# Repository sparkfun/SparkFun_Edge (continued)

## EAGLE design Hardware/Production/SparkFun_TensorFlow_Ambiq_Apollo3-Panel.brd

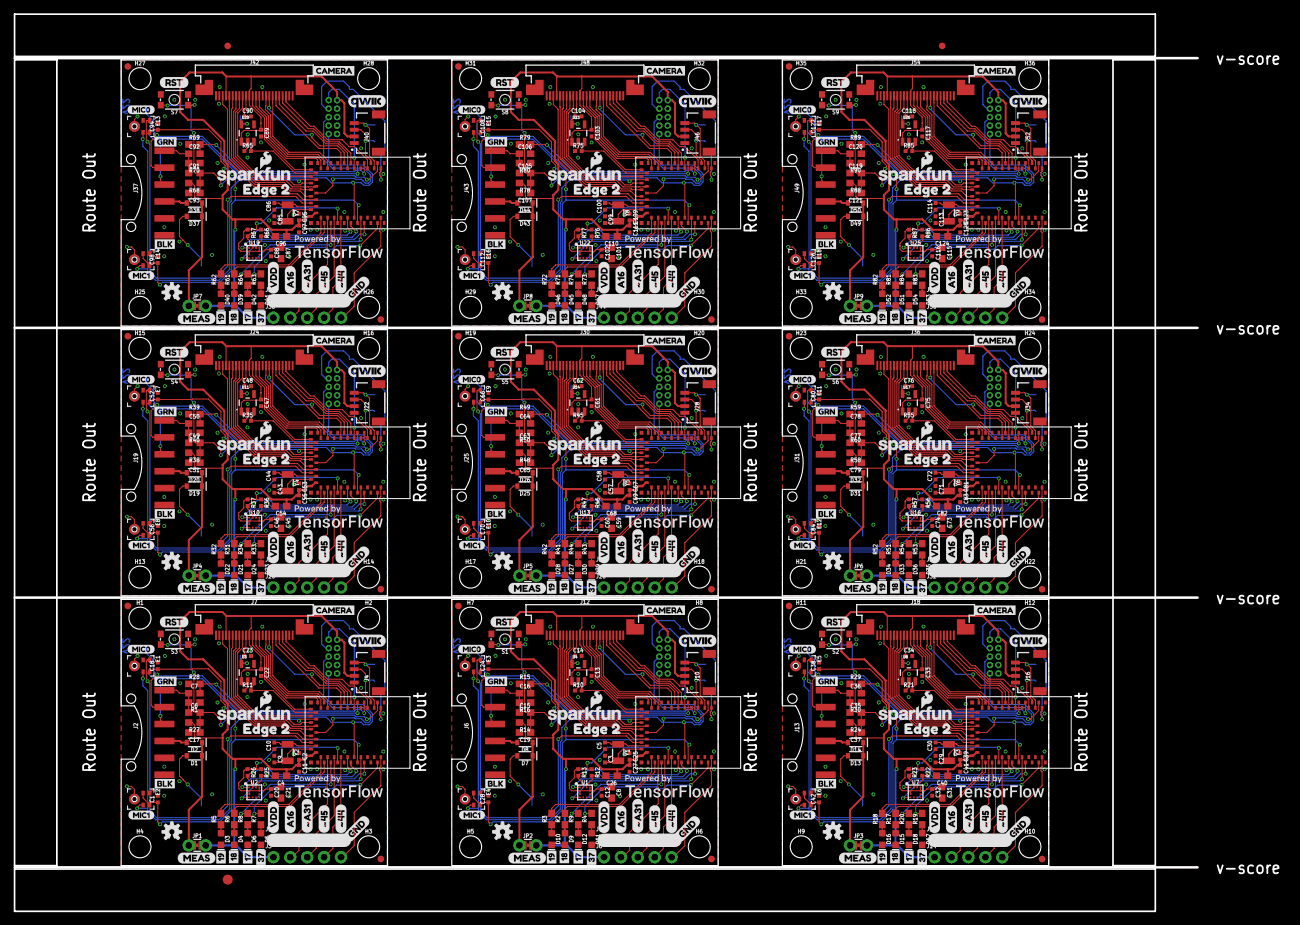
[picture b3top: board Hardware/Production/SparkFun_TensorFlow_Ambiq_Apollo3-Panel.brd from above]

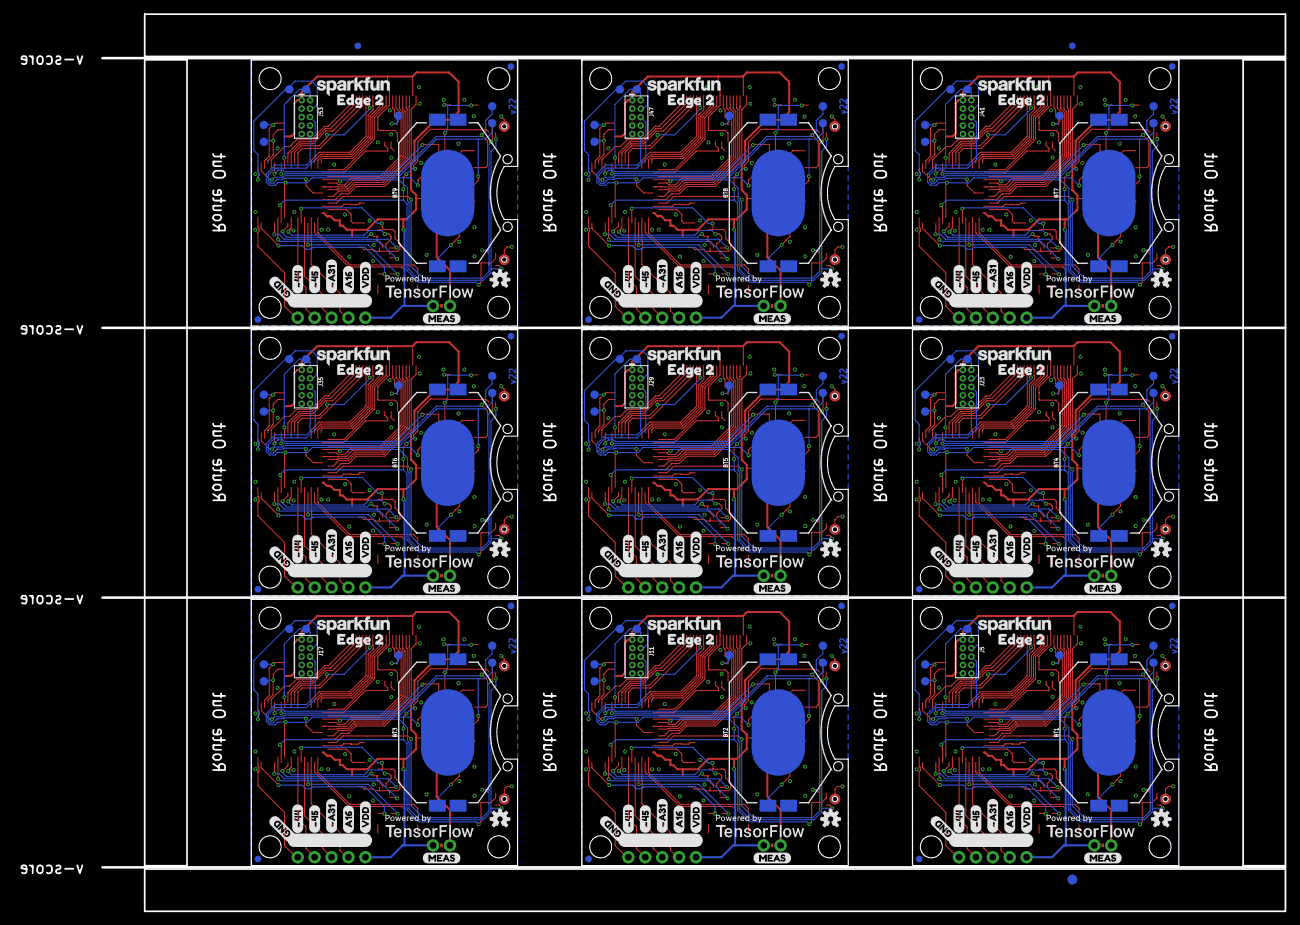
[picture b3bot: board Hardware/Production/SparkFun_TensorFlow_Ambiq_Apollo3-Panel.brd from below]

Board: 2 copper layers, 177.7 x 134.7 mm, 861 parts (201 on the bottom side), 495 nets.

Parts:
BT1, BT2, BT3, BT4, BT5, BT6, BT7, BT8, BT9: BATTCON_20MM_4LEGS_OVERPASTE_INNER
C1, C2, C12, C18, C20, C24, C25, C28, C32, C38, C39, C42, C46, C52, C53, C56, C60, C66, C67, C70, C74, C80, C81, C84, C88, C94, C95, C98, C102, C108, C109, C112, C116, C122, C123, C126: 0.1uF; 0402-TIGHT
C3, C5, C9, C10, C29, C30, C43, C44, C57, C58, C71, C72, C85, C86, C99, C100, C113, C114: 15pF; 0402-TIGHT
C4, C8, C21, C26, C31, C40, C45, C54, C59, C68, C73, C82, C87, C96, C101, C110, C115, C124: 10uF; 0603
C6, C7, C15, C16, C35, C36, C49, C50, C63, C64, C77, C78, C91, C92, C105, C106, C119, C120: 0.1uF; 0603
C11, C13, C14, C22, C23, C27, C33, C34, C41, C47, C48, C55, C61, C62, C69, C75, C76, C83, C89, C90, C97, C103, C104, C111, C117, C118, C125: 1.0uF; 0402-TIGHT
C17, C19, C37, C51, C65, C79, C93, C107, C121: 1nF; 0603
D1, D2, D7, D8, D13, D14, D19, D20, D25, D26, D31, D32, D37, D38, D43, D44, D49, D50: 1A/23V/620mV; SOD-323
D3, D10, D16, D22, D28, D34, D40, D46, D52: RED; LED-0603
D4, D9, D15, D21, D27, D33, D39, D45, D51: BLUE; LED-0603
D5, D11, D17, D23, D29, D35, D41, D47, D53: Yellow; LED-0603
D6, D12, D18, D24, D30, D36, D42, D48, D54: GREEN; LED-0603
E1, E2, E3, E4, E5, E6, E7, E8, E9, E10, E11, E12, E13, E14, E15, E16, E17, E18: SPH0641LM4H-1; SPH0641LM4H-1_MICROPHONE
E$1, E$2, E$3, E$4: FIDUCIAL-1X2
E$5, E$6: FIDUCIAL-1.5X3
FD1, FD2, FD3, FD4, FD5, FD6, FD7, FD8, FD9, FD10, FD11, FD12, FD13, FD14, FD15, FD16, FD17, FD18, FD19, FD20, FD21, FD22, FD23, FD24, FD25, FD26, FD27, FD28, FD29, FD30, FD31, FD32, FD33, FD34, FD35, FD36: FIDUCIAL1X2; FIDUCIAL-1X2
FRAME1, FRAME3, FRAME5, FRAME7, FRAME9, FRAME11, FRAME13, FRAME15, FRAME17: FRAME-LETTER; CREATIVE_COMMONS
FRAME2, FRAME4, FRAME6, FRAME8, FRAME10, FRAME12, FRAME14, FRAME16, FRAME18: FRAME-LETTERNO_PACKAGE; DUMMY
H1, H2, H3, H4, H5, H6, H7, H8, H9, H10, H11, H12, H13, H14, H15, H16, H17, H18, H19, H20, H21, H22, H23, H24, H25, H26, H27, H28, H29, H30, H31, H32, H33, H34, H35, H36: STAND-OFF
J1, J3, J8, J9, J14, J15, J20, J21, J26, J27, J32, J33, J38, J39, J44, J45, J50, J51: 1X05_NO_SILK
J2, J6, J13, J19, J25, J31, J37, J43, J49: 1X06-SMD_RA_MALE
J4, J10, J16, J22, J28, J34, J40, J46, J52: JST04_1MM_RA
J5, J11, J17, J23, J29, J35, J41, J47, J53: CORTEX_DEBUG; 2X5-PTH-1.27MM
J7, J12, J18, J24, J30, J36, J42, J48, J54: CAMERA-HIMAX; FPC-24-AMPHENOL-SFV24R-1STE1HLF
JP1, JP2, JP3, JP4, JP5, JP6, JP7, JP8, JP9: JUMPER-COMBO_2_NC_TRACE; COMBO-JUMPER_2_NC_TRACE
LOGO1, LOGO3, LOGO5, LOGO7, LOGO9, LOGO11, LOGO13, LOGO15, LOGO17: SFE_LOGO_NAME_FLAME.1_INCH; SFE_LOGO_NAME_FLAME_.1
LOGO2, LOGO4, LOGO6, LOGO8, LOGO10, LOGO12, LOGO14, LOGO16, LOGO18: OSHW-LOGOS; OSHW-LOGO-S
R1, R14, R16, R24, R27, R30, R38, R40, R48, R50, R58, R60, R68, R70, R78, R80, R88, R90: 100k; 0603
R2, R3, R4, R5, R6, R7, R8, R9, R17, R18, R19, R20, R31, R32, R33, R34, R41, R42, R43, R44, R51, R52, R53, R54, R61, R62, R63, R64, R71, R72, R73, R74, R81, R82, R83, R84: 1k; 0603
R10, R11, R12, R13, R21, R22, R23, R25, R26, R35, R36, R37, R45, R46, R47, R55, R56, R57, R65, R66, R67, R75, R76, R77, R85, R86, R87: 100k; 0402-TIGHT
R15, R28, R29, R39, R49, R59, R69, R79, R89: 220k; 0603
S1, S2, S3, S4, S5, S6, S7, S8, S9: RESET; TACTILE_SWITCH_SMD_4.6X2.8MM
TP1, TP2, TP8, TP9, TP15, TP16, TP22, TP23, TP29, TP30, TP36, TP37, TP43, TP44, TP50, TP51, TP57, TP58: PAD.03X.05
TP3, TP4, TP5, TP6, TP7, TP10, TP11, TP12, TP13, TP14, TP17, TP18, TP19, TP20, TP21, TP24, TP25, TP26, TP27, TP28, TP31, TP32, TP33, TP34, TP35, TP38, TP39, TP40, TP41, TP42, TP45, TP46, TP47, TP48, TP49, TP52, TP53, TP54, TP55, TP56, TP59, TP60, TP61, TP62, TP63: TEST-POINT3X5; PAD.03X.05
U1, U2, U7, U10, U13, U16, U19, U22, U25: LIS2DH12; LGA-12-LISDH12
U3, U4, U8, U11, U14, U17, U20, U23, U26: 1.8V; SOT23-5
U5, U6, U9, U12, U15, U18, U21, U24, U27: ARTEMIS_MODULESMD; ARTEMIS_FP
U$1, U$43, U$74, U$105, U$136, U$167, U$198, U$229, U$260: MIC00
U$2, U$37, U$68, U$99, U$130, U$161, U$192, U$223, U$254: BLK2
U$3, U$14, U$17, U$33, U$63, U$66, U$94, U$97, U$125, U$128, U$156, U$159, U$187, U$190, U$218, U$221, U$249, U$252: GND0
U$4, U$9, U$18, U$22, U$64, U$65, U$95, U$96, U$126, U$127, U$157, U$158, U$188, U$189, U$219, U$220, U$250, U$251: VDD1
U$5, U$12, U$48, U$54, U$79, U$85, U$110, U$116, U$141, U$147, U$172, U$178, U$203, U$209, U$234, U$240, U$265, U$271: #453
U$6, U$11, U$49, U$53, U$80, U$84, U$111, U$115, U$142, U$146, U$173, U$177, U$204, U$208, U$235, U$239, U$266, U$270: #A312
U$7, U$10, U$50, U$52, U$81, U$83, U$112, U$114, U$143, U$145, U$174, U$176, U$205, U$207, U$236, U$238, U$267, U$269: A161
U$8, U$51, U$82, U$113, U$144, U$175, U$206, U$237, U$268: MIC10
U$13, U$36, U$47, U$55, U$78, U$86, U$109, U$117, U$140, U$148, U$171, U$179, U$202, U$210, U$233, U$241, U$264, U$272: #444
U$15, U$32, U$56, U$60, U$87, U$91, U$118, U$122, U$149, U$153, U$180, U$184, U$211, U$215, U$242, U$246, U$273, U$277: EDGE_20
U$16, U$39, U$70, U$101, U$132, U$163, U$194, U$225, U$256: 372
U$19, U$40, U$71, U$102, U$133, U$164, U$195, U$226, U$257: QWIIC_COPYRIGHT_SMALL
U$20, U$41, U$72, U$103, U$134, U$165, U$196, U$227, U$258: CAMERA3
U$21, U$25, U$42, U$44, U$73, U$75, U$104, U$106, U$135, U$137, U$166, U$168, U$197, U$199, U$228, U$230, U$259, U$261: POWEREDBY_TF#JPG
U$23, U$57, U$88, U$119, U$150, U$181, U$212, U$243, U$274: 171
U$24, U$35, U$61, U$62, U$92, U$93, U$123, U$124, U$154, U$155, U$185, U$186, U$216, U$217, U$247, U$248, U$278, U$279: MEAS10
U$26, U$58, U$89, U$120, U$151, U$182, U$213, U$244, U$275: 182
U$27, U$34, U$67, U$98, U$129, U$160, U$191, U$222, U$253: RST15
U$28, U$38, U$69, U$100, U$131, U$162, U$193, U$224, U$255: GRN1
U$29, U$45, U$76, U$107, U$138, U$169, U$200, U$231, U$262: SFE_LOGO_NAME_.1
U$30, U$46, U$77, U$108, U$139, U$170, U$201, U$232, U$263: OSHW-LOGO-S
U$31, U$59, U$90, U$121, U$152, U$183, U$214, U$245, U$276: 193
Y1, Y2, Y3, Y4, Y5, Y6, Y7, Y8, Y9: 32.768kHz; CRYSTAL-SMD-3.2X1.5MM

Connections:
1.8V: C23.1, J7.10, TP7.P$1, U3.5
1.8V1: C14.1, J12.10, TP14.P$1, U4.5
1.8V2: C34.1, J18.10, TP21.P$1, U8.5
1.8V3: C48.1, J24.10, TP28.P$1, U11.5
1.8V4: C62.1, J30.10, TP35.P$1, U14.5
1.8V5: C76.1, J36.10, TP42.P$1, U17.5
1.8V6: C90.1, J42.10, TP49.P$1, U20.5
1.8V7: C104.1, J48.10, TP56.P$1, U23.5
1.8V8: C118.1, J54.10, TP63.P$1, U26.5
!DTR: C6.1, C7.1, J2.1, R1.2
!DTR1: C15.1, C16.1, J6.1, R16.2
!DTR2: C35.1, C36.1, J13.1, R30.2
!DTR3: C49.1, C50.1, J19.1, R40.2
!DTR4: C63.1, C64.1, J25.1, R50.2
!DTR5: C77.1, C78.1, J31.1, R60.2
!DTR6: C91.1, C92.1, J37.1, R70.2
!DTR7: C105.1, C106.1, J43.1, R80.2
!DTR8: C119.1, C120.1, J49.1, R90.2
A1: J8.2, U6.AD16
A2: J14.2, U9.AD16
A3: J20.2, U12.AD16
A4: J26.2, U15.AD16
A5: J32.2, U18.AD16
A6: J38.2, U21.AD16
A7: J44.2, U24.AD16
A8: J50.2, U27.AD16
A16: J3.2, U5.AD16
ACCEL_I2C_SCL: U2.1, U5.~D42
ACCEL_I2C_SCL1: U1.1, U6.~D42
ACCEL_I2C_SCL2: U7.1, U9.~D42
ACCEL_I2C_SCL3: U10.1, U12.~D42
ACCEL_I2C_SCL4: U13.1, U15.~D42
ACCEL_I2C_SCL5: U16.1, U18.~D42
ACCEL_I2C_SCL6: U19.1, U21.~D42
ACCEL_I2C_SCL7: U22.1, U24.~D42
ACCEL_I2C_SCL8: U25.1, U27.~D42
ACCEL_I2C_SDA: U2.4, U5.~D43
ACCEL_I2C_SDA1: U1.4, U6.~D43
ACCEL_I2C_SDA2: U7.4, U9.~D43
ACCEL_I2C_SDA3: U10.4, U12.~D43
ACCEL_I2C_SDA4: U13.4, U15.~D43
ACCEL_I2C_SDA5: U16.4, U18.~D43
ACCEL_I2C_SDA6: U19.4, U21.~D43
ACCEL_I2C_SDA7: U22.4, U24.~D43
ACCEL_I2C_SDA8: U25.4, U27.~D43
ACCEL_INT1: R26.2, U2.12, U5.D2
ACCEL_INT2: R25.2, U2.11, U5.D1
ACCEL_INT3: R13.2, U1.12, U6.D2
ACCEL_INT4: R12.2, U1.11, U6.D1
ACCEL_INT5: R23.2, U7.12, U9.D2
ACCEL_INT6: R22.2, U7.11, U9.D1
ACCEL_INT7: R37.2, U10.12, U12.D2
ACCEL_INT8: R36.2, U10.11, U12.D1
ACCEL_INT9: R47.2, U13.12, U15.D2
ACCEL_INT10: R46.2, U13.11, U15.D1
ACCEL_INT11: R57.2, U16.12, U18.D2
ACCEL_INT12: R56.2, U16.11, U18.D1
ACCEL_INT13: R67.2, U19.12, U21.D2
ACCEL_INT14: R66.2, U19.11, U21.D1
ACCEL_INT15: R77.2, U22.12, U24.D2
ACCEL_INT16: R76.2, U22.11, U24.D1
ACCEL_INT17: R87.2, U25.12, U27.D2
ACCEL_INT18: R86.2, U25.11, U27.D1
AMBIQ_!RST: C6.2, C17.1, J5.10, R27.1, S3.3, S3.4, U5.~RST
AMBIQ_!RST1: C15.2, C19.1, J11.10, R14.1, S1.3, S1.4, U6.~RST
AMBIQ_!RST2: C35.2, C37.1, J17.10, R24.1, S2.3, S2.4, U9.~RST
AMBIQ_!RST3: C49.2, C51.1, J23.10, R38.1, S4.3, S4.4, U12.~RST
AMBIQ_!RST4: C63.2, C65.1, J29.10, R48.1, S5.3, S5.4, U15.~RST
AMBIQ_!RST5: C77.2, C79.1, J35.10, R58.1, S6.3, S6.4, U18.~RST
AMBIQ_!RST6: C91.2, C93.1, J41.10, R68.1, S7.3, S7.4, U21.~RST
AMBIQ_!RST7: C105.2, C107.1, J47.10, R78.1, S8.3, S8.4, U24.~RST
AMBIQ_!RST8: C119.2, C121.1, J53.10, R88.1, S9.3, S9.4, U27.~RST
BOOT: C7.2, R28.2, U5.BOOT
BOOT1: C16.2, R15.2, U6.BOOT
BOOT2: C36.2, R29.2, U9.BOOT
BOOT3: C50.2, R39.2, U12.BOOT
BOOT4: C64.2, R49.2, U15.BOOT
BOOT5: C78.2, R59.2, U18.BOOT
BOOT6: C92.2, R69.2, U21.BOOT
BOOT7: C106.2, R79.2, U24.BOOT
BOOT8: C120.2, R89.2, U27.BOOT
CAMERA_D0: J7.14, U5.D14
CAMERA_D1: J7.3, U5.~AD11
CAMERA_D2: J7.9, U5.~D25
CAMERA_D3: J7.5, U5.AD34
CAMERA_D4: J7.12, U5.~D6
CAMERA_D5: J7.20, U5.~D5
CAMERA_D6: J7.19, U5.~AD35
CAMERA_D7: J7.13, U5.~D28
CAMERA_D8: J12.5, U6.AD34
CAMERA_D9: J12.3, U6.~AD11
CAMERA_D10: J12.9, U6.~D25
CAMERA_D11: J12.12, U6.~D6
CAMERA_D12: J12.14, U6.D14
CAMERA_D13: J12.13, U6.~D28
CAMERA_D14: J12.19, U6.~AD35
CAMERA_D15: J12.20, U6.~D5
CAMERA_D16: J18.5, U9.AD34
CAMERA_D17: J18.3, U9.~AD11
CAMERA_D18: J18.9, U9.~D25
CAMERA_D19: J18.12, U9.~D6
CAMERA_D20: J18.14, U9.D14
CAMERA_D21: J18.13, U9.~D28
CAMERA_D22: J18.19, U9.~AD35
CAMERA_D23: J18.20, U9.~D5
CAMERA_D24: J24.5, U12.AD34
CAMERA_D25: J24.3, U12.~AD11
CAMERA_D26: J24.9, U12.~D25
CAMERA_D27: J24.12, U12.~D6
CAMERA_D28: J24.14, U12.D14
CAMERA_D29: J24.13, U12.~D28
CAMERA_D30: J24.19, U12.~AD35
CAMERA_D31: J24.20, U12.~D5
CAMERA_D32: J30.5, U15.AD34
CAMERA_D33: J30.3, U15.~AD11
CAMERA_D34: J30.9, U15.~D25
CAMERA_D35: J30.12, U15.~D6
CAMERA_D36: J30.14, U15.D14
CAMERA_D37: J30.13, U15.~D28
CAMERA_D38: J30.19, U15.~AD35
CAMERA_D39: J30.20, U15.~D5
CAMERA_D40: J36.5, U18.AD34
CAMERA_D41: J36.3, U18.~AD11
CAMERA_D42: J36.9, U18.~D25
CAMERA_D43: J36.12, U18.~D6
CAMERA_D44: J36.14, U18.D14
CAMERA_D45: J36.13, U18.~D28
CAMERA_D46: J36.19, U18.~AD35
CAMERA_D47: J36.20, U18.~D5
CAMERA_D48: J42.5, U21.AD34
CAMERA_D49: J42.3, U21.~AD11
CAMERA_D50: J42.9, U21.~D25
CAMERA_D51: J42.12, U21.~D6
CAMERA_D52: J42.14, U21.D14
CAMERA_D53: J42.13, U21.~D28
CAMERA_D54: J42.19, U21.~AD35
CAMERA_D55: J42.20, U21.~D5
CAMERA_D56: J48.5, U24.AD34
CAMERA_D57: J48.3, U24.~AD11
CAMERA_D58: J48.9, U24.~D25
CAMERA_D59: J48.12, U24.~D6
CAMERA_D60: J48.14, U24.D14
CAMERA_D61: J48.13, U24.~D28
CAMERA_D62: J48.19, U24.~AD35
CAMERA_D63: J48.20, U24.~D5
CAMERA_D64: J54.5, U27.AD34
CAMERA_D65: J54.3, U27.~AD11
CAMERA_D66: J54.9, U27.~D25
CAMERA_D67: J54.12, U27.~D6
CAMERA_D68: J54.14, U27.D14
CAMERA_D69: J54.13, U27.~D28
CAMERA_D70: J54.19, U27.~AD35
CAMERA_D71: J54.20, U27.~D5
CAMERA_DVDD_EN: R11.2, U3.3, U5.~AD32
CAMERA_DVDD_EN1: R10.2, U4.3, U6.~AD32
CAMERA_DVDD_EN2: R21.2, U8.3, U9.~AD32
CAMERA_DVDD_EN3: R35.2, U11.3, U12.~AD32
CAMERA_DVDD_EN4: R45.2, U14.3, U15.~AD32
CAMERA_DVDD_EN5: R55.2, U17.3, U18.~AD32
CAMERA_DVDD_EN6: R65.2, U20.3, U21.~AD32
CAMERA_DVDD_EN7: R75.2, U23.3, U24.~AD32
CAMERA_DVDD_EN8: R85.2, U26.3, U27.~AD32
CAMERA_HSYNC: J7.16, U5.~D27
CAMERA_HSYNC1: J12.16, U6.~D27
CAMERA_HSYNC2: J18.16, U9.~D27
CAMERA_HSYNC3: J24.16, U12.~D27
CAMERA_HSYNC4: J30.16, U15.~D27
CAMERA_HSYNC5: J36.16, U18.~D27
CAMERA_HSYNC6: J42.16, U21.~D27
CAMERA_HSYNC7: J48.16, U24.~D27
CAMERA_HSYNC8: J54.16, U27.~D27
CAMERA_I2C_SCL: J7.21, U5.D8
CAMERA_I2C_SCL1: J12.21, U6.D8
CAMERA_I2C_SCL2: J18.21, U9.D8
CAMERA_I2C_SCL3: J24.21, U12.D8
CAMERA_I2C_SCL4: J30.21, U15.D8
CAMERA_I2C_SCL5: J36.21, U18.D8
CAMERA_I2C_SCL6: J42.21, U21.D8
CAMERA_I2C_SCL7: J48.21, U24.D8
CAMERA_I2C_SCL8: J54.21, U27.D8
CAMERA_I2C_SDA: J7.22, U5.D9
CAMERA_I2C_SDA1: J12.22, U6.D9
CAMERA_I2C_SDA2: J18.22, U9.D9
CAMERA_I2C_SDA3: J24.22, U12.D9
CAMERA_I2C_SDA4: J30.22, U15.D9
CAMERA_I2C_SDA5: J36.22, U18.D9
CAMERA_I2C_SDA6: J42.22, U21.D9
CAMERA_I2C_SDA7: J48.22, U24.D9
CAMERA_I2C_SDA8: J54.22, U27.D9
CAMERA_INT: J7.18, U5.~D23
CAMERA_INT1: J12.18, U6.~D23
CAMERA_INT2: J18.18, U9.~D23
CAMERA_INT3: J24.18, U12.~D23
CAMERA_INT4: J30.18, U15.~D23
CAMERA_INT5: J36.18, U18.~D23
CAMERA_INT6: J42.18, U21.~D23
CAMERA_INT7: J48.18, U24.~D23
CAMERA_INT8: J54.18, U27.~D23
CAMERA_MCLK: J7.8, U5.~D26
CAMERA_MCLK1: J12.8, U6.~D26
CAMERA_MCLK2: J18.8, U9.~D26
CAMERA_MCLK3: J24.8, U12.~D26
CAMERA_MCLK4: J30.8, U15.~D26
CAMERA_MCLK5: J36.8, U18.~D26
CAMERA_MCLK6: J42.8, U21.~D26
CAMERA_MCLK7: J48.8, U24.~D26
CAMERA_MCLK8: J54.8, U27.~D26
CAMERA_PCLK: J7.17, U5.D7
CAMERA_PCLK1: J12.17, U6.D7
CAMERA_PCLK2: J18.17, U9.D7
CAMERA_PCLK3: J24.17, U12.D7
CAMERA_PCLK4: J30.17, U15.D7
CAMERA_PCLK5: J36.17, U18.D7
CAMERA_PCLK6: J42.17, U21.D7
CAMERA_PCLK7: J48.17, U24.D7
CAMERA_PCLK8: J54.17, U27.D7
CAMERA_TRIG: J7.7, U5.~AD13
CAMERA_TRIG1: J12.7, U6.~AD13
CAMERA_TRIG2: J18.7, U9.~AD13
CAMERA_TRIG3: J24.7, U12.~AD13
CAMERA_TRIG4: J30.7, U15.~AD13
CAMERA_TRIG5: J36.7, U18.~AD13
CAMERA_TRIG6: J42.7, U21.~AD13
CAMERA_TRIG7: J48.7, U24.~AD13
CAMERA_TRIG8: J54.7, U27.~AD13
CAMERA_VSYNC: J7.6, U5.D15
CAMERA_VSYNC1: J12.6, U6.D15
CAMERA_VSYNC2: J18.6, U9.D15
CAMERA_VSYNC3: J24.6, U12.D15
CAMERA_VSYNC4: J30.6, U15.D15
CAMERA_VSYNC5: J36.6, U18.D15
CAMERA_VSYNC6: J42.6, U21.D15
CAMERA_VSYNC7: J48.6, U24.D15
CAMERA_VSYNC8: J54.6, U27.D15
FTDI_VCC: D2.A, J2.4
FTDI_VCC1: D8.A, J6.4
FTDI_VCC2: D14.A, J13.4
FTDI_VCC3: D20.A, J19.4
FTDI_VCC4: D26.A, J25.4
FTDI_VCC5: D32.A, J31.4
FTDI_VCC6: D38.A, J37.4
FTDI_VCC7: D44.A, J43.4
FTDI_VCC8: D50.A, J49.4
GND: BT1.2, C1.2, C2.1, C4.2, C9.1, C10.1, C11.2, C17.2, C18.2, C20.2, C21.2, C22.2, C23.2, D3.C, D4.C, D5.C, D6.C, E1.2, E1.3, E1.6, E1.7, E1.8, E2.3, E2.6, E2.7, E2.8, J1.1, J1.2, J1.3, J1.4, J1.5, J2.6, J4.1, J5.3, J5.5, J5.9, J7.2, J7.15, R1.1, R11.1, R28.1, S3.1, S3.2, U2.5, U2.6, U2.7, U2.8, U3.2, U5.GND@1, U5.GND@22, U5.GND@38, U5.GND@39, U5.GND@47, U5.GND@59
GND1: BT2.2, C3.1, C5.1, C8.2, C12.2, C13.2, C14.2, C19.2, C24.2, C25.1, C26.2, C27.2, C28.2, D9.C, D10.C, D11.C, D12.C, E3.2, E3.3, E3.6, E3.7, E3.8, E4.3, E4.6, E4.7, E4.8, J6.6, J9.1, J9.2, J9.3, J9.4, J9.5, J10.1, J11.3, J11.5, J11.9, J12.2, J12.15, R10.1, R15.1, R16.1, S1.1, S1.2, U1.5, U1.6, U1.7, U1.8, U4.2, U6.GND@1, U6.GND@22, U6.GND@38, U6.GND@39, U6.GND@47, U6.GND@59
GND2: BT3.2, C29.1, C30.1, C31.2, C32.2, C33.2, C34.2, C37.2, C38.2, C39.1, C40.2, C41.2, C42.2, D15.C, D16.C, D17.C, D18.C, E5.2, E5.3, E5.6, E5.7, E5.8, E6.3, E6.6, E6.7, E6.8, J13.6, J15.1, J15.2, J15.3, J15.4, J15.5, J16.1, J17.3, J17.5, J17.9, J18.2, J18.15, R21.1, R29.1, R30.1, S2.1, S2.2, U7.5, U7.6, U7.7, U7.8, U8.2, U9.GND@1, U9.GND@22, U9.GND@38, U9.GND@39, U9.GND@47, U9.GND@59
GND3: BT4.2, C43.1, C44.1, C45.2, C46.2, C47.2, C48.2, C51.2, C52.2, C53.1, C54.2, C55.2, C56.2, D21.C, D22.C, D23.C, D24.C, E7.2, E7.3, E7.6, E7.7, E7.8, E8.3, E8.6, E8.7, E8.8, J19.6, J21.1, J21.2, J21.3, J21.4, J21.5, J22.1, J23.3, J23.5, J23.9, J24.2, J24.15, R35.1, R39.1, R40.1, S4.1, S4.2, U10.5, U10.6, U10.7, U10.8, U11.2, U12.GND@1, U12.GND@22, U12.GND@38, U12.GND@39, U12.GND@47, U12.GND@59
GND4: BT5.2, C57.1, C58.1, C59.2, C60.2, C61.2, C62.2, C65.2, C66.2, C67.1, C68.2, C69.2, C70.2, D27.C, D28.C, D29.C, D30.C, E9.2, E9.3, E9.6, E9.7, E9.8, E10.3, E10.6, E10.7, E10.8, J25.6, J27.1, J27.2, J27.3, J27.4, J27.5, J28.1, J29.3, J29.5, J29.9, J30.2, J30.15, R45.1, R49.1, R50.1, S5.1, S5.2, U13.5, U13.6, U13.7, U13.8, U14.2, U15.GND@1, U15.GND@22, U15.GND@38, U15.GND@39, U15.GND@47, U15.GND@59
GND5: BT6.2, C71.1, C72.1, C73.2, C74.2, C75.2, C76.2, C79.2, C80.2, C81.1, C82.2, C83.2, C84.2, D33.C, D34.C, D35.C, D36.C, E11.2, E11.3, E11.6, E11.7, E11.8, E12.3, E12.6, E12.7, E12.8, J31.6, J33.1, J33.2, J33.3, J33.4, J33.5, J34.1, J35.3, J35.5, J35.9, J36.2, J36.15, R55.1, R59.1, R60.1, S6.1, S6.2, U16.5, U16.6, U16.7, U16.8, U17.2, U18.GND@1, U18.GND@22, U18.GND@38, U18.GND@39, U18.GND@47, U18.GND@59
GND6: BT7.2, C85.1, C86.1, C87.2, C88.2, C89.2, C90.2, C93.2, C94.2, C95.1, C96.2, C97.2, C98.2, D39.C, D40.C, D41.C, D42.C, E13.2, E13.3, E13.6, E13.7, E13.8, E14.3, E14.6, E14.7, E14.8, J37.6, J39.1, J39.2, J39.3, J39.4, J39.5, J40.1, J41.3, J41.5, J41.9, J42.2, J42.15, R65.1, R69.1, R70.1, S7.1, S7.2, U19.5, U19.6, U19.7, U19.8, U20.2, U21.GND@1, U21.GND@22, U21.GND@38, U21.GND@39, U21.GND@47, U21.GND@59
GND7: BT8.2, C99.1, C100.1, C101.2, C102.2, C103.2, C104.2, C107.2, C108.2, C109.1, C110.2, C111.2, C112.2, D45.C, D46.C, D47.C, D48.C, E15.2, E15.3, E15.6, E15.7, E15.8, E16.3, E16.6, E16.7, E16.8, J43.6, J45.1, J45.2, J45.3, J45.4, J45.5, J46.1, J47.3, J47.5, J47.9, J48.2, J48.15, R75.1, R79.1, R80.1, S8.1, S8.2, U22.5, U22.6, U22.7, U22.8, U23.2, U24.GND@1, U24.GND@22, U24.GND@38, U24.GND@39, U24.GND@47, U24.GND@59
GND8: BT9.2, C113.1, C114.1, C115.2, C116.2, C117.2, C118.2, C121.2, C122.2, C123.1, C124.2, C125.2, C126.2, D51.C, D52.C, D53.C, D54.C, E17.2, E17.3, E17.6, E17.7, E17.8, E18.3, E18.6, E18.7, E18.8, J49.6, J51.1, J51.2, J51.3, J51.4, J51.5, J52.1, J53.3, J53.5, J53.9, J54.2, J54.15, R85.1, R89.1, R90.1, S9.1, S9.2, U25.5, U25.6, U25.7, U25.8, U26.2, U27.GND@1, U27.GND@22, U27.GND@38, U27.GND@39, U27.GND@47, U27.GND@59
LED_BLUE: R6.2, U5.~D18
LED_BLUE1: R2.2, U6.~D18
LED_BLUE2: R17.2, U9.~D18
LED_BLUE3: R31.2, U12.~D18
LED_BLUE4: R41.2, U15.~D18
LED_BLUE5: R51.2, U18.~D18
LED_BLUE6: R61.2, U21.~D18
LED_BLUE7: R71.2, U24.~D18
LED_BLUE8: R81.2, U27.~D18
LED_GREEN: R8.2, U5.D17
LED_GREEN1: R9.2, U6.D17
LED_GREEN2: R20.2, U9.D17
LED_GREEN3: R34.2, U12.D17
LED_GREEN4: R44.2, U15.D17
LED_GREEN5: R54.2, U18.D17
LED_GREEN6: R64.2, U21.D17
LED_GREEN7: R74.2, U24.D17
LED_GREEN8: R84.2, U27.D17
LED_RED: R5.2, U5.~D19
LED_RED1: R3.2, U6.~D19
LED_RED2: R18.2, U9.~D19
LED_RED3: R32.2, U12.~D19
LED_RED4: R42.2, U15.~D19
LED_RED5: R52.2, U18.~D19
LED_RED6: R62.2, U21.~D19
LED_RED7: R72.2, U24.~D19
LED_RED8: R82.2, U27.~D19
LED_YELLOW: R7.2, U5.~D37
LED_YELLOW1: R4.2, U6.~D37
LED_YELLOW2: R19.2, U9.~D37
LED_YELLOW3: R33.2, U12.~D37
LED_YELLOW4: R43.2, U15.~D37
LED_YELLOW5: R53.2, U18.~D37
LED_YELLOW6: R63.2, U21.~D37
LED_YELLOW7: R73.2, U24.~D37
LED_YELLOW8: R83.2, U27.~D37
MIC_CLK: E1.4, E2.4, U5.~AD12
MIC_CLK1: E3.4, E4.4, U6.~AD12
MIC_CLK2: E5.4, E6.4, U9.~AD12
MIC_CLK3: E7.4, E8.4, U12.~AD12
MIC_CLK4: E9.4, E10.4, U15.~AD12
MIC_CLK5: E11.4, E12.4, U18.~AD12
MIC_CLK6: E13.4, E14.4, U21.~AD12
MIC_CLK7: E15.4, E16.4, U24.~AD12
MIC_CLK8: E17.4, E18.4, U27.~AD12
MIC_DATA: E1.1, E2.1, U5.~AD29
MIC_DATA1: E3.1, E4.1, U6.~AD29
MIC_DATA2: E5.1, E6.1, U9.~AD29
MIC_DATA3: E7.1, E8.1, U12.~AD29
MIC_DATA4: E9.1, E10.1, U15.~AD29
MIC_DATA5: E11.1, E12.1, U18.~AD29
MIC_DATA6: E13.1, E14.1, U21.~AD29
MIC_DATA7: E15.1, E16.1, U24.~AD29
MIC_DATA8: E17.1, E18.1, U27.~AD29
unnamed: D9.A, R2.1
unnamed: C9.2, U5.XI, Y2.P$2
unnamed: D10.A, R3.1
unnamed: D11.A, R4.1
unnamed: D4.A, R6.1
unnamed: D3.A, R5.1
unnamed: D5.A, R7.1
unnamed: D6.A, R8.1
unnamed: D12.A, R9.1
unnamed: C3.2, U6.XI, Y1.P$2
unnamed: D15.A, R17.1
unnamed: D16.A, R18.1
unnamed: D17.A, R19.1
unnamed: D18.A, R20.1
unnamed: C29.2, U9.XI, Y3.P$2
unnamed: D21.A, R31.1
unnamed: D22.A, R32.1
unnamed: D23.A, R33.1
unnamed: D24.A, R34.1
unnamed: C43.2, U12.XI, Y4.P$2
unnamed: D27.A, R41.1
unnamed: D28.A, R42.1
unnamed: D29.A, R43.1
unnamed: D30.A, R44.1
unnamed: C57.2, U15.XI, Y5.P$2
unnamed: D33.A, R51.1
unnamed: D34.A, R52.1
unnamed: D35.A, R53.1
unnamed: D36.A, R54.1
unnamed: C71.2, U18.XI, Y6.P$2
unnamed: D39.A, R61.1
unnamed: D40.A, R62.1
unnamed: D41.A, R63.1
unnamed: D42.A, R64.1
unnamed: C85.2, U21.XI, Y7.P$2
unnamed: D45.A, R71.1
unnamed: D46.A, R72.1
unnamed: D47.A, R73.1
unnamed: D48.A, R74.1
unnamed: C99.2, U24.XI, Y8.P$2
unnamed: D51.A, R81.1
unnamed: D52.A, R82.1
unnamed: D53.A, R83.1
unnamed: D54.A, R84.1
unnamed: C113.2, U27.XI, Y9.P$2
QWIIC_SCL: J4.4, TP3.P$1, U5.~D39
QWIIC_SCL1: J10.4, TP10.P$1, U6.~D39
QWIIC_SCL2: J16.4, TP17.P$1, U9.~D39
QWIIC_SCL3: J22.4, TP24.P$1, U12.~D39
QWIIC_SCL4: J28.4, TP31.P$1, U15.~D39
QWIIC_SCL5: J34.4, TP38.P$1, U18.~D39
QWIIC_SCL6: J40.4, TP45.P$1, U21.~D39
QWIIC_SCL7: J46.4, TP52.P$1, U24.~D39
QWIIC_SCL8: J52.4, TP59.P$1, U27.~D39
QWIIC_SDA: J4.3, TP4.P$1, U5.D40
QWIIC_SDA1: J10.3, TP11.P$1, U6.D40
QWIIC_SDA2: J16.3, TP18.P$1, U9.D40
QWIIC_SDA3: J22.3, TP25.P$1, U12.D40
QWIIC_SDA4: J28.3, TP32.P$1, U15.D40
QWIIC_SDA5: J34.3, TP39.P$1, U18.D40
QWIIC_SDA6: J40.3, TP46.P$1, U21.D40
QWIIC_SDA7: J46.3, TP53.P$1, U24.D40
QWIIC_SDA8: J52.3, TP60.P$1, U27.D40
SWDCK: J5.4, TP1.P$1, U5.SWDCK
SWDCK1: J11.4, TP8.P$1, U6.SWDCK
SWDCK2: J17.4, TP15.P$1, U9.SWDCK
SWDCK3: J23.4, TP22.P$1, U12.SWDCK
SWDCK4: J29.4, TP29.P$1, U15.SWDCK
SWDCK5: J35.4, TP36.P$1, U18.SWDCK
SWDCK6: J41.4, TP43.P$1, U21.SWDCK
SWDCK7: J47.4, TP50.P$1, U24.SWDCK
SWDCK8: J53.4, TP57.P$1, U27.SWDCK
SWDIO: J5.2, TP2.P$1, U5.SWDIO
SWDIO1: J11.2, TP9.P$1, U6.SWDIO
SWDIO2: J17.2, TP16.P$1, U9.SWDIO
SWDIO3: J23.2, TP23.P$1, U12.SWDIO
SWDIO4: J29.2, TP30.P$1, U15.SWDIO
SWDIO5: J35.2, TP37.P$1, U18.SWDIO
SWDIO6: J41.2, TP44.P$1, U21.SWDIO
SWDIO7: J47.2, TP51.P$1, U24.SWDIO
SWDIO8: J53.2, TP58.P$1, U27.SWDIO
UART-RX: J2.3, TP6.P$1, U5.RXI-0
UART-RX1: J6.3, TP13.P$1, U6.RXI-0
UART-RX2: J13.3, TP20.P$1, U9.RXI-0
UART-RX3: J19.3, TP27.P$1, U12.RXI-0
UART-RX4: J25.3, TP34.P$1, U15.RXI-0
UART-RX5: J31.3, TP41.P$1, U18.RXI-0
UART-RX6: J37.3, TP48.P$1, U21.RXI-0
UART-RX7: J43.3, TP55.P$1, U24.RXI-0
UART-RX8: J49.3, TP62.P$1, U27.RXI-0
UART-TX: J2.2, TP5.P$1, U5.TXO-0
UART-TX1: J6.2, TP12.P$1, U6.TXO-0
UART-TX2: J13.2, TP19.P$1, U9.TXO-0
UART-TX3: J19.2, TP26.P$1, U12.TXO-0
UART-TX4: J25.2, TP33.P$1, U15.TXO-0
UART-TX5: J31.2, TP40.P$1, U18.TXO-0
UART-TX6: J37.2, TP47.P$1, U21.TXO-0
UART-TX7: J43.2, TP54.P$1, U24.TXO-0
UART-TX8: J49.2, TP61.P$1, U27.TXO-0
VDD: C2.2, C4.1, C11.1, C22.1, J3.1, J4.2, J5.1, J7.4, J7.11, JP1.2, JP1.4, R27.2, U3.1, U5.VDD@36, U5.VDD@37
VDD1: C13.1, C25.2, C26.1, C27.1, J8.1, J10.2, J11.1, J12.4, J12.11, JP2.2, JP2.4, R14.2, U4.1, U6.VDD@36, U6.VDD@37
VDD2: C33.1, C39.2, C40.1, C41.1, J14.1, J16.2, J17.1, J18.4, J18.11, JP3.2, JP3.4, R24.2, U8.1, U9.VDD@36, U9.VDD@37
VDD3: C47.1, C53.2, C54.1, C55.1, J20.1, J22.2, J23.1, J24.4, J24.11, JP4.2, JP4.4, R38.2, U11.1, U12.VDD@36, U12.VDD@37
VDD4: C61.1, C67.2, C68.1, C69.1, J26.1, J28.2, J29.1, J30.4, J30.11, JP5.2, JP5.4, R48.2, U14.1, U15.VDD@36, U15.VDD@37
VDD5: C75.1, C81.2, C82.1, C83.1, J32.1, J34.2, J35.1, J36.4, J36.11, JP6.2, JP6.4, R58.2, U17.1, U18.VDD@36, U18.VDD@37
VDD6: C89.1, C95.2, C96.1, C97.1, J38.1, J40.2, J41.1, J42.4, J42.11, JP7.2, JP7.4, R68.2, U20.1, U21.VDD@36, U21.VDD@37
VDD7: C103.1, C109.2, C110.1, C111.1, J44.1, J46.2, J47.1, J48.4, J48.11, JP8.2, JP8.4, R78.2, U23.1, U24.VDD@36, U24.VDD@37
VDD8: C117.1, C123.2, C124.1, C125.1, J50.1, J52.2, J53.1, J54.4, J54.11, JP9.2, JP9.4, R88.2, U26.1, U27.VDD@36, U27.VDD@37
VDD_ACCEL: C20.1, C21.1, R25.1, R26.1, U2.2, U2.3, U2.9, U2.10, U5.D41
VDD_ACCEL1: C8.1, C12.1, R12.1, R13.1, U1.2, U1.3, U1.9, U1.10, U6.D41
VDD_ACCEL2: C31.1, C32.1, R22.1, R23.1, U7.2, U7.3, U7.9, U7.10, U9.D41
VDD_ACCEL3: C45.1, C46.1, R36.1, R37.1, U10.2, U10.3, U10.9, U10.10, U12.D41
VDD_ACCEL4: C59.1, C60.1, R46.1, R47.1, U13.2, U13.3, U13.9, U13.10, U15.D41
VDD_ACCEL5: C73.1, C74.1, R56.1, R57.1, U16.2, U16.3, U16.9, U16.10, U18.D41
VDD_ACCEL6: C87.1, C88.1, R66.1, R67.1, U19.2, U19.3, U19.9, U19.10, U21.D41
VDD_ACCEL7: C101.1, C102.1, R76.1, R77.1, U22.2, U22.3, U22.9, U22.10, U24.D41
VDD_ACCEL8: C115.1, C116.1, R86.1, R87.1, U25.2, U25.3, U25.9, U25.10, U27.D41
VDD_PDM: C1.1, C18.1, E1.5, E2.2, E2.5, U5.D0
VDD_PDM1: C24.1, C28.1, E3.5, E4.2, E4.5, U6.D0
VDD_PDM2: C38.1, C42.1, E5.5, E6.2, E6.5, U9.D0
VDD_PDM3: C52.1, C56.1, E7.5, E8.2, E8.5, U12.D0
VDD_PDM4: C66.1, C70.1, E9.5, E10.2, E10.5, U15.D0
VDD_PDM5: C80.1, C84.1, E11.5, E12.2, E12.5, U18.D0
VDD_PDM6: C94.1, C98.1, E13.5, E14.2, E14.5, U21.D0
VDD_PDM7: C108.1, C112.1, E15.5, E16.2, E16.5, U24.D0
VDD_PDM8: C122.1, C126.1, E17.5, E18.2, E18.5, U27.D0
VIN1: D1.C, D2.C, JP1.1, JP1.3
VIN2: D7.C, D8.C, JP2.1, JP2.3
VIN3: D13.C, D14.C, JP3.1, JP3.3
VIN4: D19.C, D20.C, JP4.1, JP4.3
VIN5: D25.C, D26.C, JP5.1, JP5.3
VIN6: D31.C, D32.C, JP6.1, JP6.3
VIN7: D37.C, D38.C, JP7.1, JP7.3
VIN8: D43.C, D44.C, JP8.1, JP8.3
VIN9: D49.C, D50.C, JP9.1, JP9.3
V_BATT: BT1.1, D1.A
V_BATT1: BT2.1, D7.A
V_BATT2: BT3.1, D13.A
V_BATT3: BT4.1, D19.A
V_BATT4: BT5.1, D25.A
V_BATT5: BT6.1, D31.A
V_BATT6: BT7.1, D37.A
V_BATT7: BT8.1, D43.A
V_BATT8: BT9.1, D49.A
X0: C10.2, U5.XO, Y2.P$1
X1: C5.2, U6.XO, Y1.P$1
X2: C30.2, U9.XO, Y3.P$1
X3: C44.2, U12.XO, Y4.P$1
X4: C58.2, U15.XO, Y5.P$1
X5: C72.2, U18.XO, Y6.P$1
X6: C86.2, U21.XO, Y7.P$1
X7: C100.2, U24.XO, Y8.P$1
X8: C114.2, U27.XO, Y9.P$1
~1: J8.4, U6.~D45
~2: J8.5, U6.~D44
~3: J14.4, U9.~D45
~4: J14.5, U9.~D44
~5: J20.4, U12.~D45
~6: J20.5, U12.~D44
~7: J26.4, U15.~D45
~8: J26.5, U15.~D44
~9: J32.4, U18.~D45
~10: J32.5, U18.~D44
~11: J38.4, U21.~D45
~12: J38.5, U21.~D44
~13: J44.4, U24.~D45
~14: J44.5, U24.~D44
~15: J50.4, U27.~D45
~16: J50.5, U27.~D44
~44: J3.5, U5.~D44
~45: J3.4, U5.~D45
~A1: J8.3, U6.~AD31
~A2: J14.3, U9.~AD31
~A3: J20.3, U12.~AD31
~A4: J26.3, U15.~AD31
~A5: J32.3, U18.~AD31
~A6: J38.3, U21.~AD31
~A7: J44.3, U24.~AD31
~A8: J50.3, U27.~AD31
~A31: J3.3, U5.~AD31
~AD33/SWO: J5.6, U5.~AD33/SWO
~AD33/SWO1: J11.6, U6.~AD33/SWO
~AD33/SWO2: J17.6, U9.~AD33/SWO
~AD33/SWO3: J23.6, U12.~AD33/SWO
~AD33/SWO4: J29.6, U15.~AD33/SWO
~AD33/SWO5: J35.6, U18.~AD33/SWO
~AD33/SWO6: J41.6, U21.~AD33/SWO
~AD33/SWO7: J47.6, U24.~AD33/SWO
~AD33/SWO8: J53.6, U27.~AD33/SWO

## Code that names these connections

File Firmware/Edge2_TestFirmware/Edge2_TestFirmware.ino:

/* Author: Nathan Seidle
  Created: Septempter 19th, 2019
  License: MIT. See SparkFun Arduino Apollo3 Project for more information

  This example demonstrates the following:
    Activate 1.8V vreg
    Ping Accel
    Ping mics
    Twinkle LEDs
    Drive Qwiic pins
*/

#include <Wire.h>

#include "SparkFun_LIS2DH12.h"

SPARKFUN_LIS2DH12 accel; //Create instance of object

#define ACCEL_ADDRESS 0x19 //On the Edge and Edge2 the accelerometer is address 0x19

unsigned long lastTimeCheck = 0;

#define QWIIC_SCL 39
#define QWIIC_SDA 30

#define VDD_CAMERA 32
#define VDD_PDM 0 //Only available on v2.2 PCB and above
#define VDD_ACCEL 41 //Only available on v2.2 PCB and above

//-=-=-= Vars for PDM -=-=-=-

//Global variables needed for PDM library
#define pdmDataBufferSize 4096 //Default is array of 4096 * 32bit
uint32_t pdmDataBuffer[pdmDataBufferSize];

//Global variables needed for the FFT in this sketch
float g_fPDMTimeDomain[pdmDataBufferSize * 2];
float g_fPDMFrequencyDomain[pdmDataBufferSize * 2];
float g_fPDMMagnitudes[pdmDataBufferSize * 2];
uint32_t sampleFreq;

//Enable these defines for additional debug printing
#define PRINT_PDM_DATA 0
#define PRINT_FFT_DATA 0

#include <PDM.h> //Include PDM library included with the Aruino_Apollo3 core
AP3_PDM myPDM; //Create instance of PDM class

//Math library needed for FFT
#define ARM_MATH_CM4
#include <arm_math.h>

//-=-=-=- End Vars for PDM -=-=-=-

bool accelGood = false;
bool micGood = false;

void setup()
{
  Serial.begin(9600);
  Serial.println("SparkFun Accel Example");

  pinMode(LED_GREEN, OUTPUT);
  pinMode(LED_RED, OUTPUT);
  pinMode(LED_YELLOW, OUTPUT);
  pinMode(LED_BLUE, OUTPUT);
  digitalWrite(LED_GREEN, LOW);
  digitalWrite(LED_RED, LOW);
  digitalWrite(LED_YELLOW, HIGH);
  digitalWrite(LED_BLUE, HIGH);

  pinMode(VDD_CAMERA, OUTPUT);
  digitalWrite(VDD_CAMERA, HIGH); //Power up camera 1.8V regulator.

  //Normally we would not drive the SDA/SCL lines directly on the Qwiic connector (Wire)
  //but the test jig is just looking for continuity
  pinMode(QWIIC_SCL, OUTPUT);
  digitalWrite(QWIIC_SCL, LOW);
  pinMode(QWIIC_SDA, OUTPUT);
  digitalWrite(QWIIC_SDA, HIGH);

  pinMode(VDD_ACCEL, OUTPUT);
  digitalWrite(VDD_ACCEL, HIGH); //Power up accel. Only available on v2.2 PCB and above.

  Wire1.begin(); //Accel is on IOM3 and defined in the variant file as Wire1.

  //By default the SparkFun library uses Wire. We need to begin
  //with Wire1 on the Edge/Edge2.
  if (accel.begin(ACCEL_ADDRESS, Wire1) == false)
  {
    Serial.println("Accelerometer not detected. Are you sure you did a Wire1.begin()? Freezing...");
    while (1);
  }

  pinMode(VDD_PDM, OUTPUT);
  digitalWrite(VDD_PDM, HIGH); //Power up mics. Only available on v2.2 PCB and above.

  if (myPDM.begin() == false) // Turn on PDM with default settings
  {
    Serial.println("PDM Init failed. Are you sure these pins are PDM capable?");
    while (1);
  }
  Serial.println("PDM Initialized");

  printPDMConfig();

  myPDM.getData(pdmDataBuffer, pdmDataBufferSize); //This clears the current PDM FIFO and starts DMA
}

void loop()
{
  //Toggle LEDs and Qwiic pins
  if (millis() - lastTimeCheck > 1000)
  {
    lastTimeCheck = millis();

    if (digitalRead(LED_GREEN) == LOW)
    {
      digitalWrite(LED_GREEN, HIGH);
      digitalWrite(LED_RED, HIGH);
      digitalWrite(LED_YELLOW, LOW);
      digitalWrite(LED_BLUE, LOW);

      digitalWrite(QWIIC_SCL, HIGH);
      digitalWrite(QWIIC_SDA, LOW);
    }
    else
    {
      digitalWrite(LED_GREEN, LOW);
      digitalWrite(LED_RED, LOW);
      digitalWrite(LED_YELLOW, HIGH);
      digitalWrite(LED_BLUE, HIGH);

      digitalWrite(QWIIC_SCL, LOW);
      digitalWrite(QWIIC_SDA, HIGH);
    }
  }

  //Wait for new accel data
  while(accel.available() == false) ;

    float accelX = accel.getX();
    float accelY = accel.getY();
    float accelZ = accel.getZ();
    if (accelZ > 500.0) accelGood = true;
    
    float tempC = accel.getTemperature();

    Serial.print("Acc [mg]: ");
    Serial.print(accelX, 1);
    Serial.print(" x, ");
    Serial.print(accelY, 1);
    Serial.print(" y, ");
    Serial.print(accelZ, 1);
    Serial.print(" z, ");
    Serial.print(tempC, 1);
    Serial.print("C");

  //Wait for new PDM data
  while(myPDM.available() == false) ;

    noInterrupts();
    printLoudest();

    while (PRINT_PDM_DATA || PRINT_FFT_DATA);

    // Start converting the next set of PCM samples.
    myPDM.getData(pdmDataBuffer, pdmDataBufferSize);
    interrupts();

  if(accelGood && micGood) Serial.println(" Accel/Mic Good");
}

//*****************************************************************************
//
// Analyze and print frequency data.
//
//*****************************************************************************
void printLoudest(void)
{
  float fMaxValue;
  uint32_t ui32MaxIndex;
  int16_t *pi16PDMData = (int16_t *) pdmDataBuffer;
  uint32_t ui32LoudestFrequency;

  //
  // Convert the PDM samples to floats, and arrange them in the format
  // required by the FFT function.
  //
  for (uint32_t i = 0; i < pdmDataBufferSize; i++)
  {
    if (PRINT_PDM_DATA)
    {
      Serial.printf("%d\n", pi16PDMData[i]);
    }

    g_fPDMTimeDomain[2 * i] = pi16PDMData[i] / 1.0;
    g_fPDMTimeDomain[2 * i + 1] = 0.0;
  }

  if (PRINT_PDM_DATA)
  {
    Serial.printf("END\n");
  }

  //
  // Perform the FFT.
  //
  arm_cfft_radix4_instance_f32 S;
  arm_cfft_radix4_init_f32(&S, pdmDataBufferSize, 0, 1);
  arm_cfft_radix4_f32(&S, g_fPDMTimeDomain);
  arm_cmplx_mag_f32(g_fPDMTimeDomain, g_fPDMMagnitudes, pdmDataBufferSize);

  if (PRINT_FFT_DATA)
  {
    for (uint32_t i = 0; i < pdmDataBufferSize / 2; i++)
    {
      Serial.printf("%f\n", g_fPDMMagnitudes[i]);
    }

    Serial.printf("END\n");
  }

  //
  // Find the frequency bin with the largest magnitude.
  //
  arm_max_f32(g_fPDMMagnitudes, pdmDataBufferSize / 2, &fMaxValue, &ui32MaxIndex);

  ui32LoudestFrequency = (sampleFreq * ui32MaxIndex) / pdmDataBufferSize;

  if (PRINT_FFT_DATA)
  {
    Serial.printf("Loudest frequency bin: %d\n", ui32MaxIndex);
  }

  Serial.printf(" Loudest frequency: %d", ui32LoudestFrequency);

  if(ui32LoudestFrequency > 0) micGood = true;
}

//*****************************************************************************
//
// Print PDM configuration data.
//
//*****************************************************************************
void printPDMConfig(void)
{
  uint32_t PDMClk;
  uint32_t MClkDiv;
  float frequencyUnits;

  //
  // Read the config structure to figure out what our internal clock is set
  // to.
  //
  switch (myPDM.getClockDivider())
  {
    case AM_HAL_PDM_MCLKDIV_4: MClkDiv = 4; break;
    case AM_HAL_PDM_MCLKDIV_3: MClkDiv = 3; break;
    case AM_HAL_PDM_MCLKDIV_2: MClkDiv = 2; break;
    case AM_HAL_PDM_MCLKDIV_1: MClkDiv = 1; break;

    default:
      MClkDiv = 0;
  }

  switch (myPDM.getClockSpeed())
  {
    case AM_HAL_PDM_CLK_12MHZ:  PDMClk = 12000000; break;
    case AM_HAL_PDM_CLK_6MHZ:   PDMClk =  6000000; break;
    case AM_HAL_PDM_CLK_3MHZ:   PDMClk =  3000000; break;
    case AM_HAL_PDM_CLK_1_5MHZ: PDMClk =  1500000; break;
    case AM_HAL_PDM_CLK_750KHZ: PDMClk =   750000; break;
    case AM_HAL_PDM_CLK_375KHZ: PDMClk =   375000; break;
    case AM_HAL_PDM_CLK_187KHZ: PDMClk =   187000; break;

    default:
      PDMClk = 0;
  }

  //
  // Record the effective sample frequency. We'll need it later to print the
  // loudest frequency from the sample.
  //
  sampleFreq = (PDMClk / (MClkDiv * 2 * myPDM.getDecimationRate()));

  frequencyUnits = (float) sampleFreq / (float) pdmDataBufferSize;

  Serial.printf("Settings:\n");
  Serial.printf("PDM Clock (Hz):         %12d\n", PDMClk);
  Serial.printf("Decimation Rate:        %12d\n", myPDM.getDecimationRate());
  Serial.printf("Effective Sample Freq.: %12d\n", sampleFreq);
  Serial.printf("FFT Length:             %12d\n\n", pdmDataBufferSize);
  Serial.printf("FFT Resolution: %15.3f Hz\n", frequencyUnits);
}
